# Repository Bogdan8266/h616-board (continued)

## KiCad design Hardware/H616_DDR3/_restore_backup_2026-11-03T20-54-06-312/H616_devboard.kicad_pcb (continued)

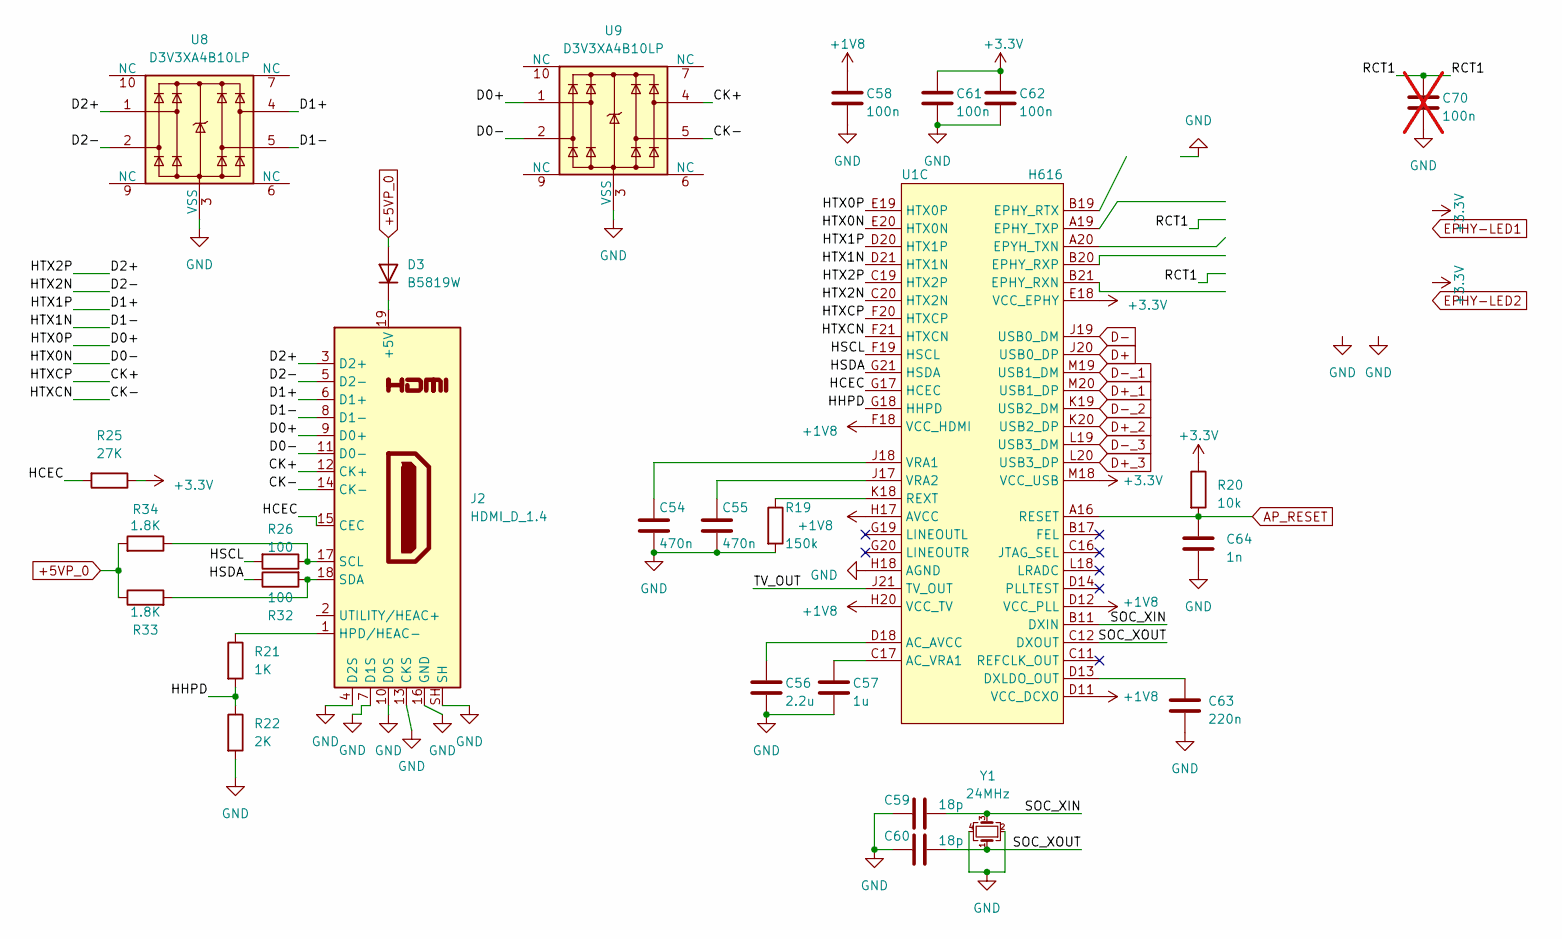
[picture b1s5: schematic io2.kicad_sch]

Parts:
C54, C55: 470n; C_0402_1005Metric
C56: 2.2u; C_0402_1005Metric
C57: 1u; C_0402_1005Metric
C58, C61, C62: 100n; C_0402_1005Metric
C59, C60: 18p; C_0402_1005Metric
C63: 220n; C_0402_1005Metric
C64: 1n; C_0402_1005Metric
C70: 100n; C_0402_1005Metric; not fitted
D3: B5819W; D_SOD-123
J2: HDMI_D_1.4; HDMI_Micro-D_Molex_46765-1xxx
R19: 150k; R_0402_1005Metric
R20: 10k; R_0402_1005Metric
R21: 1K; R_0402_1005Metric
R22: 2K; R_0402_1005Metric
R25: 27K; R_0402_1005Metric
R26, R32: 100; R_0402_1005Metric
R33, R34: 1.8K; R_0402_1005Metric
U1: H616; H616_TFBGA284
U8, U9: D3V3XA4B10LP; Diodes_UDFN-10_1x2.5mm_P0.5mm
Y1: 24MHz; Crystal_SMD_2520-4Pin_2.5x2.0mm

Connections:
+1V8: C58.1, U1.D11 (VCC_DCXO), U1.D12 (VCC_PLL), U1.F18 (VCC_HDMI), U1.H17 (AVCC), U1.H20 (VCC_TV); also elsewhere on the board
+3.3V: C61.1, C62.1, R20.1, R25.1, U1.E18 (VCC_EPHY), U1.M18 (VCC_USB); also elsewhere on the board
+5VP: D3.2 (A), R33.1, R34.2; also elsewhere on the board
/IO2/CK+: J2.12 (CK+), U1.F20 (HTXCP), U9.4
/IO2/CK-: J2.14 (CK-), U1.F21 (HTXCN), U9.5
/IO2/D0+: J2.9 (D0+), U1.E19 (HTX0P), U9.1
/IO2/D0-: J2.11 (D0-), U1.E20 (HTX0N), U9.2
/IO2/D1+: J2.6 (D1+), U1.D20 (HTX1P), U8.4
/IO2/D1-: J2.8 (D1-), U1.D21 (HTX1N), U8.5
/IO2/D2+: J2.3 (D2+), U1.C19 (HTX2P), U8.1
/IO2/D2-: J2.5 (D2-), U1.C20 (HTX2N), U8.2
/IO2/HCEC: J2.15 (CEC), R25.2, U1.G17 (HCEC)
/IO2/HHPD: R21.2, R22.1, U1.G18 (HHPD)
/IO2/HSCL: R26.2, U1.F19 (HSCL)
/IO2/HSDA: R32.1, U1.G21 (HSDA)
/IO2/RCT1: C70.1
/IO2/SOC_XIN: C59.2, U1.B11 (DXIN), Y1.3
/IO2/SOC_XOUT: C60.2, U1.C12 (DXOUT), Y1.1
/IO2/TV_OUT: U1.J21 (TV_OUT)
AP_RESET: C64.1, R20.2, U1.A16 (RESET); also elsewhere on the board
D+: U1.J20 (USB0_DP); also elsewhere on the board
D+_1: U1.M20 (USB1_DP); also elsewhere on the board
D+_2: U1.K20 (USB2_DP); also elsewhere on the board
D+_3: U1.L20 (USB3_DP); also elsewhere on the board
D-: U1.J19 (USB0_DM); also elsewhere on the board
D-_1: U1.M19 (USB1_DM); also elsewhere on the board
D-_2: U1.K19 (USB2_DM); also elsewhere on the board
D-_3: U1.L19 (USB3_DM); also elsewhere on the board
GND: C54.2, C55.2, C56.2, C57.2, C58.2, C59.1, C60.1, C61.2, C62.2, C63.2, C64.2, C70.2, J2.4 (D2S), J2.7 (D1S), J2.10 (D0S), J2.13 (CKS), J2.16 (GND), J2.SH, R19.2, R22.2, U1.H18 (AGND), U8.3 (VSS), U8.8 (VSS), U9.3 (VSS), U9.8 (VSS), Y1.2, Y1.4; also elsewhere on the board
unnamed: D3.1 (K), J2.19 (+5V)
unnamed: J2.1 (HPD/HEAC-), R21.1
unnamed: J2.17 (SCL), R26.1, R34.1
unnamed: J2.18 (SDA), R32.2, R33.2
unnamed: C56.1, U1.D18 (AC_AVCC)
unnamed: C57.1, U1.C17 (AC_VRA1)
unnamed: C63.1, U1.D13 (DXLDO_OUT)
unnamed: R19.1, U1.K18 (REXT)
unnamed: C54.1, U1.J18 (VRA1)
unnamed: C55.1, U1.J17 (VRA2)

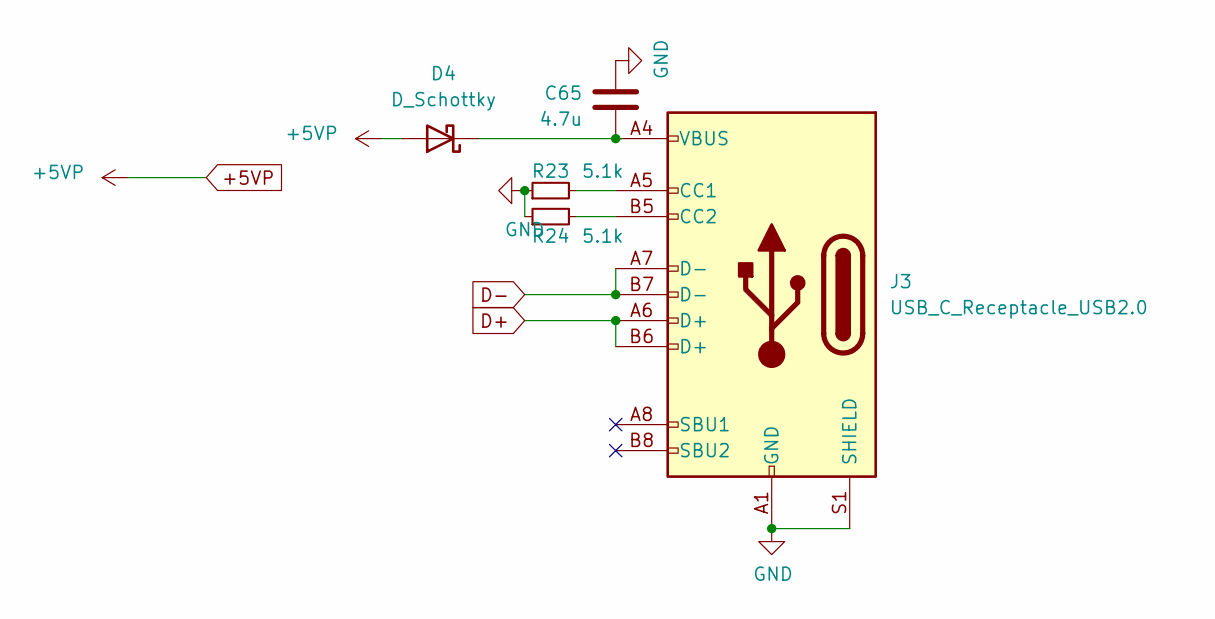
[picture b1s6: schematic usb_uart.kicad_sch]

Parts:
C65: 4.7u; C_0402_1005Metric
D4: D_Schottky; D_SOD-323_HandSoldering
J3: USB_C_Receptacle_USB2.0; USB_C_Receptacle_Palconn_UTC16-G
R23, R24: 5.1k; R_0402_1005Metric

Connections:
+5VP: D4.2 (A); also elsewhere on the board
D+: J3.A6 (D+), J3.B6 (D+); also elsewhere on the board
D-: J3.A7 (D-), J3.B7 (D-); also elsewhere on the board
GND: C65.1, J3.A1 (GND), J3.A12 (GND), J3.B1 (GND), J3.B12 (GND), J3.S1 (SHIELD), R23.1, R24.1; also elsewhere on the board
unnamed: C65.2, D4.1 (K), J3.A4 (VBUS), J3.A9 (VBUS), J3.B4 (VBUS), J3.B9 (VBUS)
unnamed: J3.A5 (CC1), R23.2
unnamed: J3.B5 (CC2), R24.2

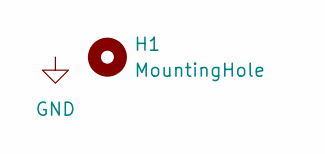
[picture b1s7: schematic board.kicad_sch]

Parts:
H1: MountingHole; MountingHole_2.5mm_Pad_Via

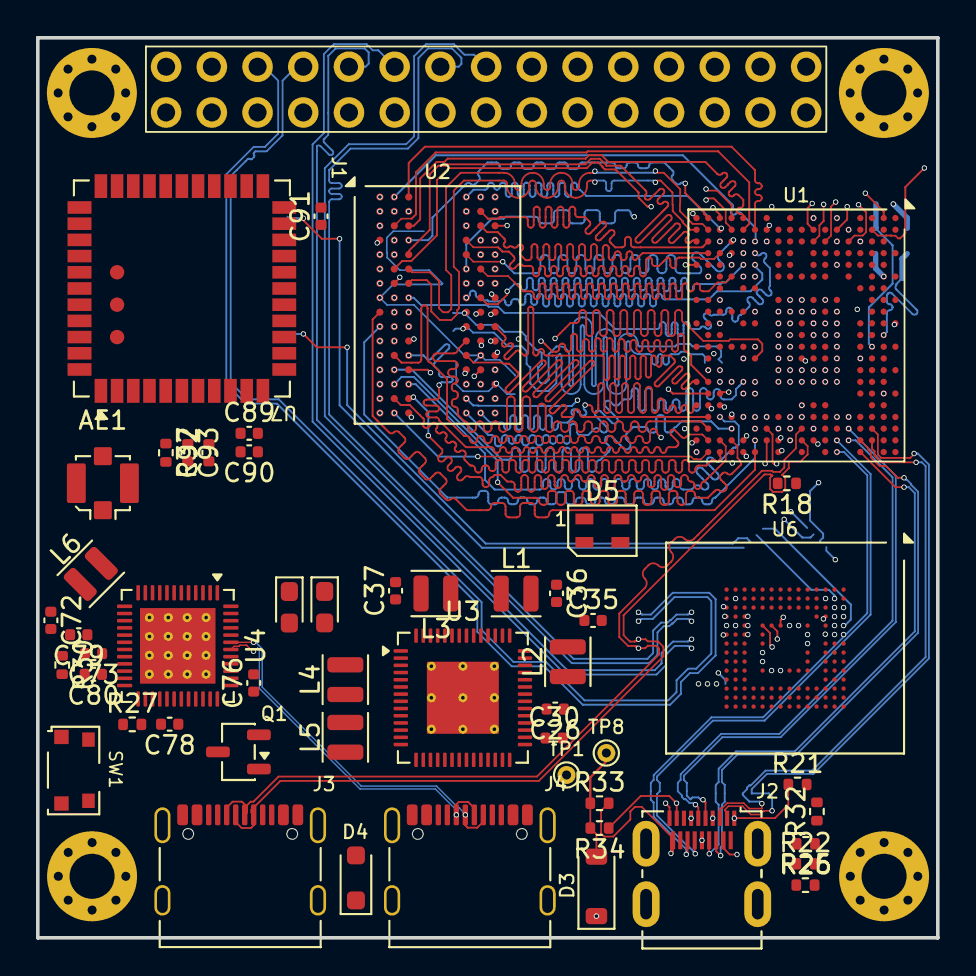
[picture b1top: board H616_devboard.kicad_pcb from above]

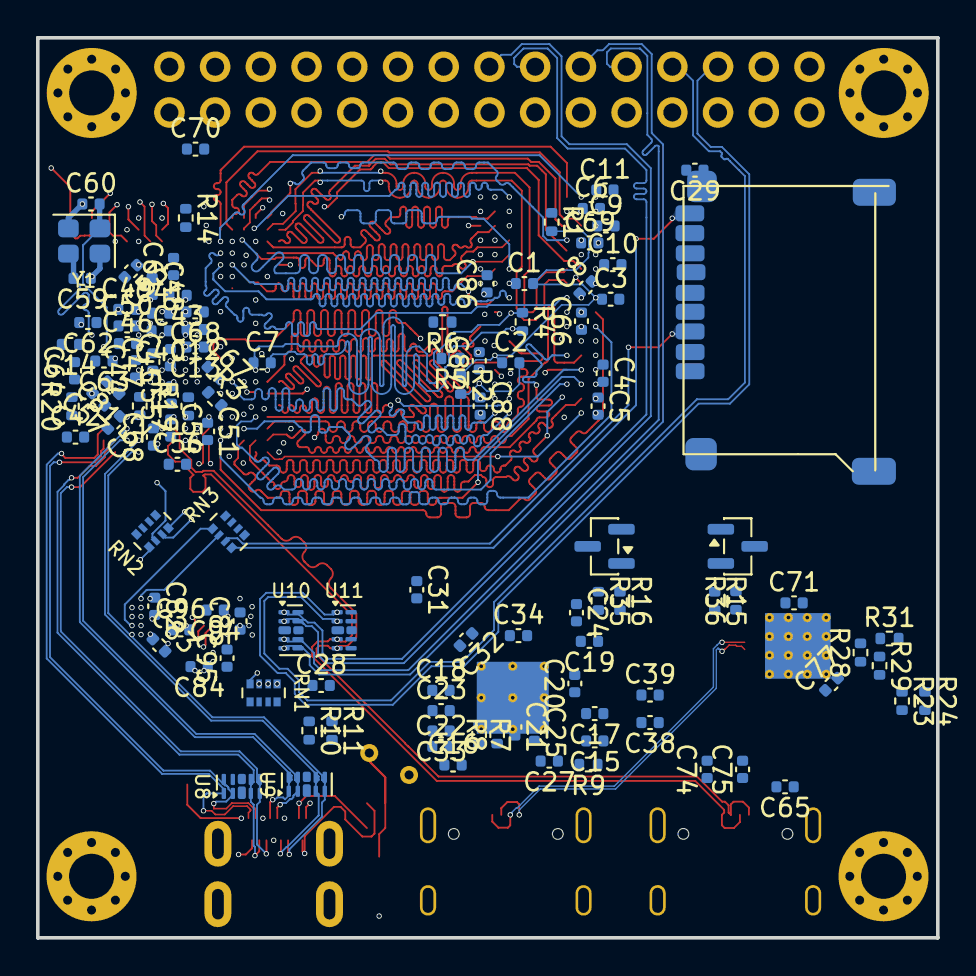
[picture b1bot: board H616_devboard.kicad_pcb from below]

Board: 8 copper layers, 50.0 x 50.0 mm, 172 parts (114 on the bottom side), 192 nets.

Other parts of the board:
H1#2, H2, H4: MountingHole; MountingHole_2.5mm_Pad_Via

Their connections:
GND: H1#2.1, H2.1, H4.1; also elsewhere on the board
